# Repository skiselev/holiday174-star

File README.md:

# Minimalist Computing - Holiday Design Contest

This project is my submission for the Facebook's Minimalist Computing group Holiday Design Contest.

## Design Contest Rules
* Holiday related design
* Can use one 7400-series IC. The logic family does not matter. It can be HC, LS, etc.
* Can use 2 transistors maximum
* Any number of passive components: capacitors, resistors, diodes, coils, LEDs (without any ICs in the LED packages, e.g. self-flashing or color changing LEDs)
* The only external connection is the power supply

## My Design's Description

My design is an eight pointed star with animated LEDs. The shape is inspired by the [Vintage Computing Christmas Challenge 2022](https://logiker.com/Vintage-Computing-Christmas-Challenge-2022).

The [design](KiCad/star-schematic-1.0.pdf) includes:
* A [multivibrator](https://en.wikipedia.org/wiki/Multivibrator), implemented using two transistors - Q1 and Q2, four resistors - R50-R53, and two capacitors - C2 and C3. The multivibrator provides the clock for the rest of the circuit.
  * The choosen values of the R52, R53 - 62 k, C2 and C3 - 2.2 uF result in approximately 5.3 Hz frequency.
  * The formula to calculate the frequency is f = 1 / (ln(2)(R52\*C2+R53\*C3)), or since R52 = R53 and C2 = C3, it can be simplified to f ~= 0.72/(R52*C2).
* A 4 bit [Johnson counter](https://en.wikipedia.org/wiki/Ring_counter), implemented using a 74*175 - four D-type flip-flops IC.
  * In my own build I used the [74LS175](https://www.ti.com/lit/ds/symlink/sn74ls174.pdf) IC, but I think any other series will work just as well.
* 3 outputs of the counter are connected to the LEDs through current limiting resistors. The last output is not connected to the LEDs. This doubles the delay when all LEDs are on and when all LEDs are off.
  * The LEDs are connected between the inverted outputs of the flip-flops and VCC. This is because TTL/TTL-LS series ICs have the low-level output current I<sub>OL</sub> much higher than the high-level output current I<sub>OH</sub>. For the 74LS175 the values are 16 mA and -800 uA respectively.
  * The current limiting resistors have a fairly large resistance. I used 4.7 k for red LEDs and 10k for green and blue LEDs. This keeps the current well within the IC's I<sub>OL</sub> specifications.

## Design Files

* [Schematic](KiCad/star-schematic-1.0.pdf)
* [PCB Layout](KiCad/star-board-1.0.pdf)

## Bill of Materials

[Holiday174-Star project on Mouser.com](https://www.mouser.com/ProjectManager/ProjectDetail.aspx?AccessID=de9819fc8b) - View and order all components except of the PCB and the power supply. Note, the LEDs are somewhat expensive at Mouser. Use Amazon link in the BoM below - a kit with 250 color LEDs for under $8.

Component type     | Reference | Description                                 | Quantity | Possible sources and notes 
------------------ | --------- | ------------------------------------------- | -------- | --------------------------
PCB                |           | Star PCB - SK103                            | 1        | Buy from my Tindie store: Order from a PCB manufacturer of your choice using provided Gerber or KiCad files
Integrated Circuit | U1        | 74LS175 - Quadruple D-type flip-flop with reset, 16 pin DIP | 1 | Mouser [595-SN74LS175N](https://www.mouser.com/ProductDetail/595-SN74LS175N)
Transistor         | Q1, Q2    | 2N3904                                      | 1        | Mouser [512-2N3904TA](https://www.mouser.com/ProductDetail/512-2N3904TA)
LEDs               | D1 - D49  | 3 mm LEDs                                   | 49       | Amazon [3mm Led Lights, 250Pcs](https://www.amazon.com/dp/B0C5HZ6W99), Mouser [710-151033RS03000](https://www.mouser.com/ProductDetail/710-151033RS03000) - red, [710-151033GS03000](https://www.mouser.com/ProductDetail/710-151033GS03000) - green, [710-151033BS03000](https://www.mouser.com/ProductDetail/710-151033BS03000) - blue. Notes: You can use a variety of colors. Current limiting resistors might need to be adjusted to keep the brightness of the LEDs with different colors roughly the same.
Connector          | J1        | 2 pin header, 2.54 mm pitch, right angle    | 1        | Mouser [649-1012937990202BLF](https://www.mouser.com/ProductDetail/649-1012937990202BLF)
Capacitor          | C1        | 0.1 uF, 50V, MLCC, 5 mm pitch               | 1        | Mouser [810-FG28X7R1H104KNT6](https://www.mouser.com/ProductDetail/810-FG28X7R1H104KNT6)
Capacitor          | C2, C3    | 2.2 uF, MLCC, 5 mm pitch                    | 1        | Mouser [810-FG28X5R1E225KRT6](https://www.mouser.com/ProductDetail/810-FG28X5R1E225KRT6)
Capacitor          | C4        | 47 uF, 10V, Electrolytic, 6.3 mm diameter, 2.5 mm pitch | 1 | Mouser [667-EEA-GA1C470](https://www.mouser.com/ProductDetail/667-EEA-GA1C470)
Resistor           | R1 - R49  | 4.7 kohm - 10 kohm, 0.25 W, axial           | 49        | Mouser [603-CFR-25JB-52-4K7](https://www.mouser.com/ProductDetail/603-CFR-25JB-52-4K7) - 4.7k, Mouser [603-CFR-25JB-52-10K](https://www.mouser.com/ProductDetail/603-CFR-25JB-52-10K) - 10k. Adjust R1-R49 values for the desired LED brightness. It is recommended to use resistors with 4.7k resistance or above. 10k resistors work really nice with blue and bright green LEDs. 4.7k resistors work great with red LEDs
Resistor           | R50, R51  | 4.7 kohm, 0.25 W, axial                     | 2        | Mouser [603-CFR-25JB-52-4K7](https://www.mouser.com/ProductDetail/603-CFR-25JB-52-4K7)
Resistor           | R52, R53  | 62 kohm, 0.25 W, axial                      | 2        | Mouser [603-CFR-25JB-52-62K](https://www.mouser.com/ProductDetail/603-CFR-25JB-52-62K)
Power supply       |           | 5V regulated power supply                   | 1        | USB charger or similar should work. 3 x AA batteries can be used instead

## Licensing

The hardware design, including schematic and PCB layout design files are licensed under the strongly-reciprocal variant of [CERN Open Hardware Licence version 2](license-cern_ohl_s_v2.txt).

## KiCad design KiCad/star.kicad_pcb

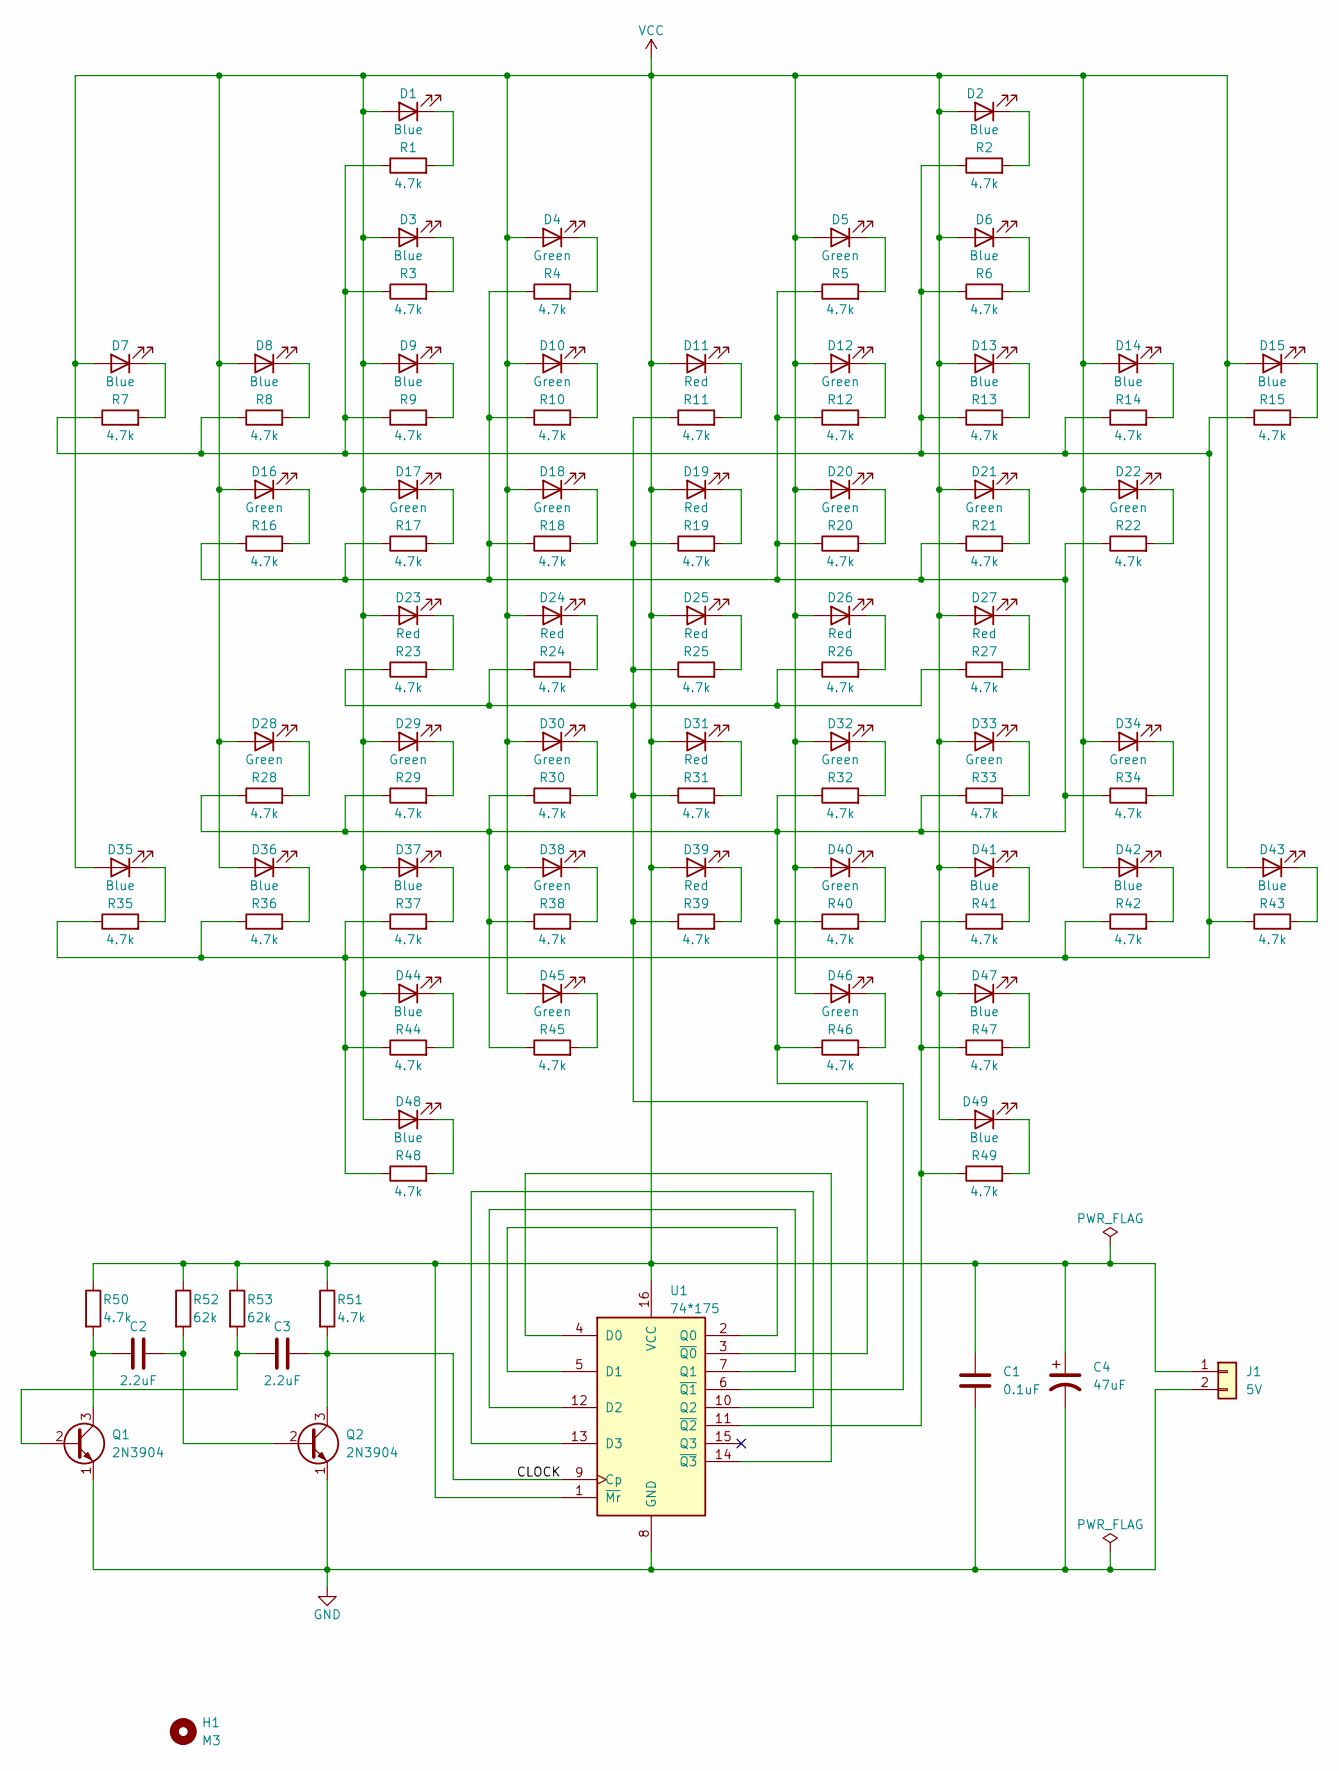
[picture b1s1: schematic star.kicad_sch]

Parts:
C1: 0.1uF; C_Rect_L7.0mm_W2.0mm_P5.00mm
C2, C3: 2.2uF; C_Rect_L7.0mm_W2.0mm_P5.00mm
C4: 47uF; CP_Radial_D5.0mm_P2.50mm
D1, D2, D3, D6, D7, D8, D9, D13, D14, D15, D35, D36, D37, D41, D42, D43, D44, D47, D48, D49: Blue; LED_D3.0mm_Clear
D4, D5, D10, D12, D16, D17, D18, D20, D21, D22, D28, D29, D30, D32, D33, D34, D38, D40, D45, D46: Green; LED_D3.0mm_Clear
D11, D19, D23, D24, D25, D26, D27, D31, D39: Red; LED_D3.0mm_Clear
H1: M3; MountingHole_3.2mm_M3_DIN965
J1: 5V; PinHeader_1x02_P2.54mm_Horizontal
Q1, Q2: 2N3904; TO-92_Inline_Wide
R1, R2, R3, R4, R5, R6, R7, R8, R9, R10, R11, R12, R13, R14, R15, R16, R17, R18, R19, R20, R21, R22, R23, R24, R25, R26, R27, R28, R29, R30, R31, R32, R33, R34, R35, R36, R37, R38, R39, R40, R41, R42, R43, R44, R45, R46, R47, R48, R49, R50, R51: 4.7k; R_Axial_DIN0207_L6.3mm_D2.5mm_P7.62mm_Horizontal
R52, R53: 62k; R_Axial_DIN0207_L6.3mm_D2.5mm_P7.62mm_Horizontal
U1: 74*175; DIP-16_W7.62mm

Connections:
/CLOCK: C3.2, Q2.3 (C), R51.2, U1.9 (Cp)
GND: C1.2, C4.2, J1.2, Q1.1 (E), Q2.1 (E), U1.8 (GND)
unnamed: C2.1, Q1.3 (C), R50.2
unnamed: C2.2, Q2.2 (B), R52.2
unnamed: C3.1, Q1.2 (B), R53.2
unnamed: D1.1 (K), R1.2
unnamed: D2.1 (K), R2.2
unnamed: D3.1 (K), R3.2
unnamed: D4.1 (K), R4.2
unnamed: D5.1 (K), R5.2
unnamed: D6.1 (K), R6.2
unnamed: D7.1 (K), R7.2
unnamed: D8.1 (K), R8.2
unnamed: D9.1 (K), R9.2
unnamed: D10.1 (K), R10.2
unnamed: D11.1 (K), R11.2
unnamed: D12.1 (K), R12.2
unnamed: D13.1 (K), R13.2
unnamed: D14.1 (K), R14.2
unnamed: D15.1 (K), R15.2
unnamed: D16.1 (K), R16.2
unnamed: D17.1 (K), R17.2
unnamed: D18.1 (K), R18.2
unnamed: D19.1 (K), R19.2
unnamed: D20.1 (K), R20.2
unnamed: D21.1 (K), R21.2
unnamed: D22.1 (K), R22.2
unnamed: D23.1 (K), R23.2
unnamed: D24.1 (K), R24.2
unnamed: D25.1 (K), R25.2
unnamed: D26.1 (K), R26.2
unnamed: D27.1 (K), R27.2
unnamed: D28.1 (K), R28.2
unnamed: D29.1 (K), R29.2
unnamed: D30.1 (K), R30.2
unnamed: D31.1 (K), R31.2
unnamed: D32.1 (K), R32.2
unnamed: D33.1 (K), R33.2
unnamed: D34.1 (K), R34.2
unnamed: D35.1 (K), R35.2
unnamed: D36.1 (K), R36.2
unnamed: D37.1 (K), R37.2
unnamed: D38.1 (K), R38.2
unnamed: D39.1 (K), R39.2
unnamed: D40.1 (K), R40.2
unnamed: D41.1 (K), R41.2
unnamed: D42.1 (K), R42.2
unnamed: D43.1 (K), R43.2
unnamed: D44.1 (K), R44.2
unnamed: D45.1 (K), R45.2
unnamed: D46.1 (K), R46.2
unnamed: D47.1 (K), R47.2
unnamed: D48.1 (K), R48.2
unnamed: D49.1 (K), R49.2
unnamed: R1.1, R2.1, R3.1, R6.1, R7.1, R8.1, R9.1, R13.1, R14.1, R15.1, R35.1, R36.1, R37.1, R41.1, R42.1, R43.1, R44.1, R47.1, R48.1, R49.1, U1.11 (~Q2)
unnamed: R4.1, R5.1, R10.1, R12.1, R16.1, R17.1, R18.1, R20.1, R21.1, R22.1, R28.1, R29.1, R30.1, R32.1, R33.1, R34.1, R38.1, R40.1, R45.1, R46.1, U1.6 (~Q1)
unnamed: R11.1, R19.1, R23.1, R24.1, R25.1, R26.1, R27.1, R31.1, R39.1, U1.3 (~Q0)
unnamed: U1.2 (Q0), U1.5 (D1)
unnamed: U1.10 (Q2), U1.13 (D3)
unnamed: U1.7 (Q1), U1.12 (D2)
unnamed: U1.4 (D0), U1.14 (~Q3)
VCC: C1.1, C4.1, D1.2 (A), D2.2 (A), D3.2 (A), D4.2 (A), D5.2 (A), D6.2 (A), D7.2 (A), D8.2 (A), D9.2 (A), D10.2 (A), D11.2 (A), D12.2 (A), D13.2 (A), D14.2 (A), D15.2 (A), D16.2 (A), D17.2 (A), D18.2 (A), D19.2 (A), D20.2 (A), D21.2 (A), D22.2 (A), D23.2 (A), D24.2 (A), D25.2 (A), D26.2 (A), D27.2 (A), D28.2 (A), D29.2 (A), D30.2 (A), D31.2 (A), D32.2 (A), D33.2 (A), D34.2 (A), D35.2 (A), D36.2 (A), D37.2 (A), D38.2 (A), D39.2 (A), D40.2 (A), D41.2 (A), D42.2 (A), D43.2 (A), D44.2 (A), D45.2 (A), D46.2 (A), D47.2 (A), D48.2 (A), D49.2 (A), J1.1, R50.1, R51.1, R52.1, R53.1, U1.1 (~Mr), U1.16 (VCC)

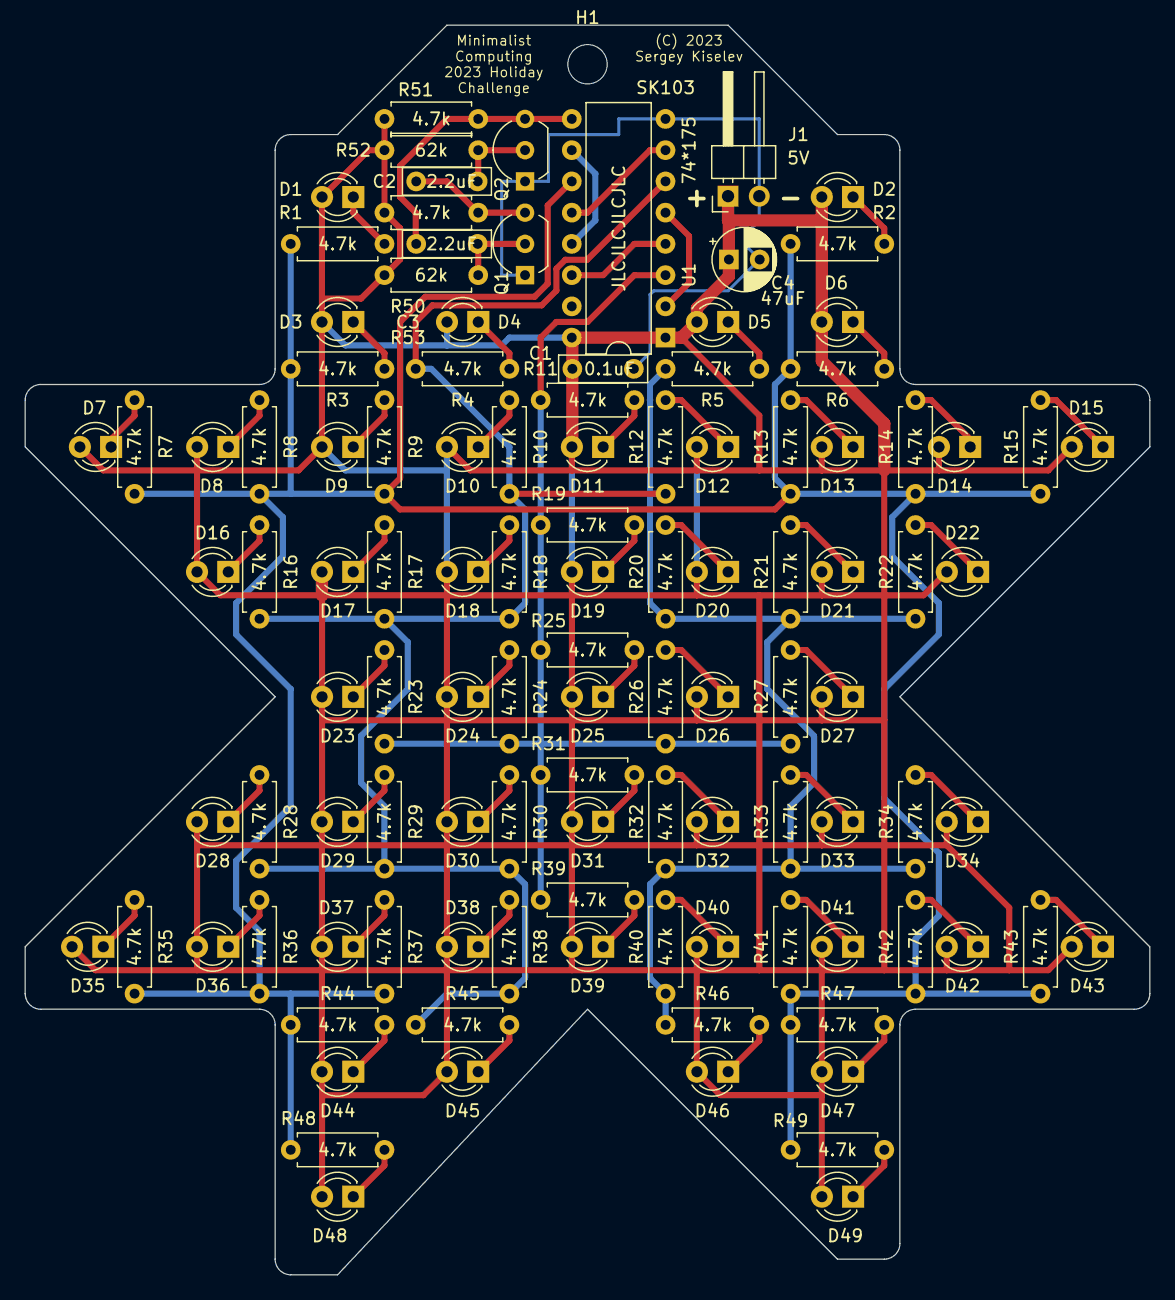
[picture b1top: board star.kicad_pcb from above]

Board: 2 copper layers, 91.4 x 101.6 mm, 112 parts (1 on the bottom side), 62 nets.

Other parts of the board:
OSHW1: OSHW-Symbol_6.7x6mm_SilkScreen

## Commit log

2023-12-18 Populate repository with design files
2023-12-18 Add the license
2023-12-18 Add PCB layout PDF
2023-12-18 Use lower resolution image
2023-12-18 Add the bill of materials

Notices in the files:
KiCad/star.kicad_pcb:
LED Star (C) 2023 Sergey Kiselev
(C) 2023
